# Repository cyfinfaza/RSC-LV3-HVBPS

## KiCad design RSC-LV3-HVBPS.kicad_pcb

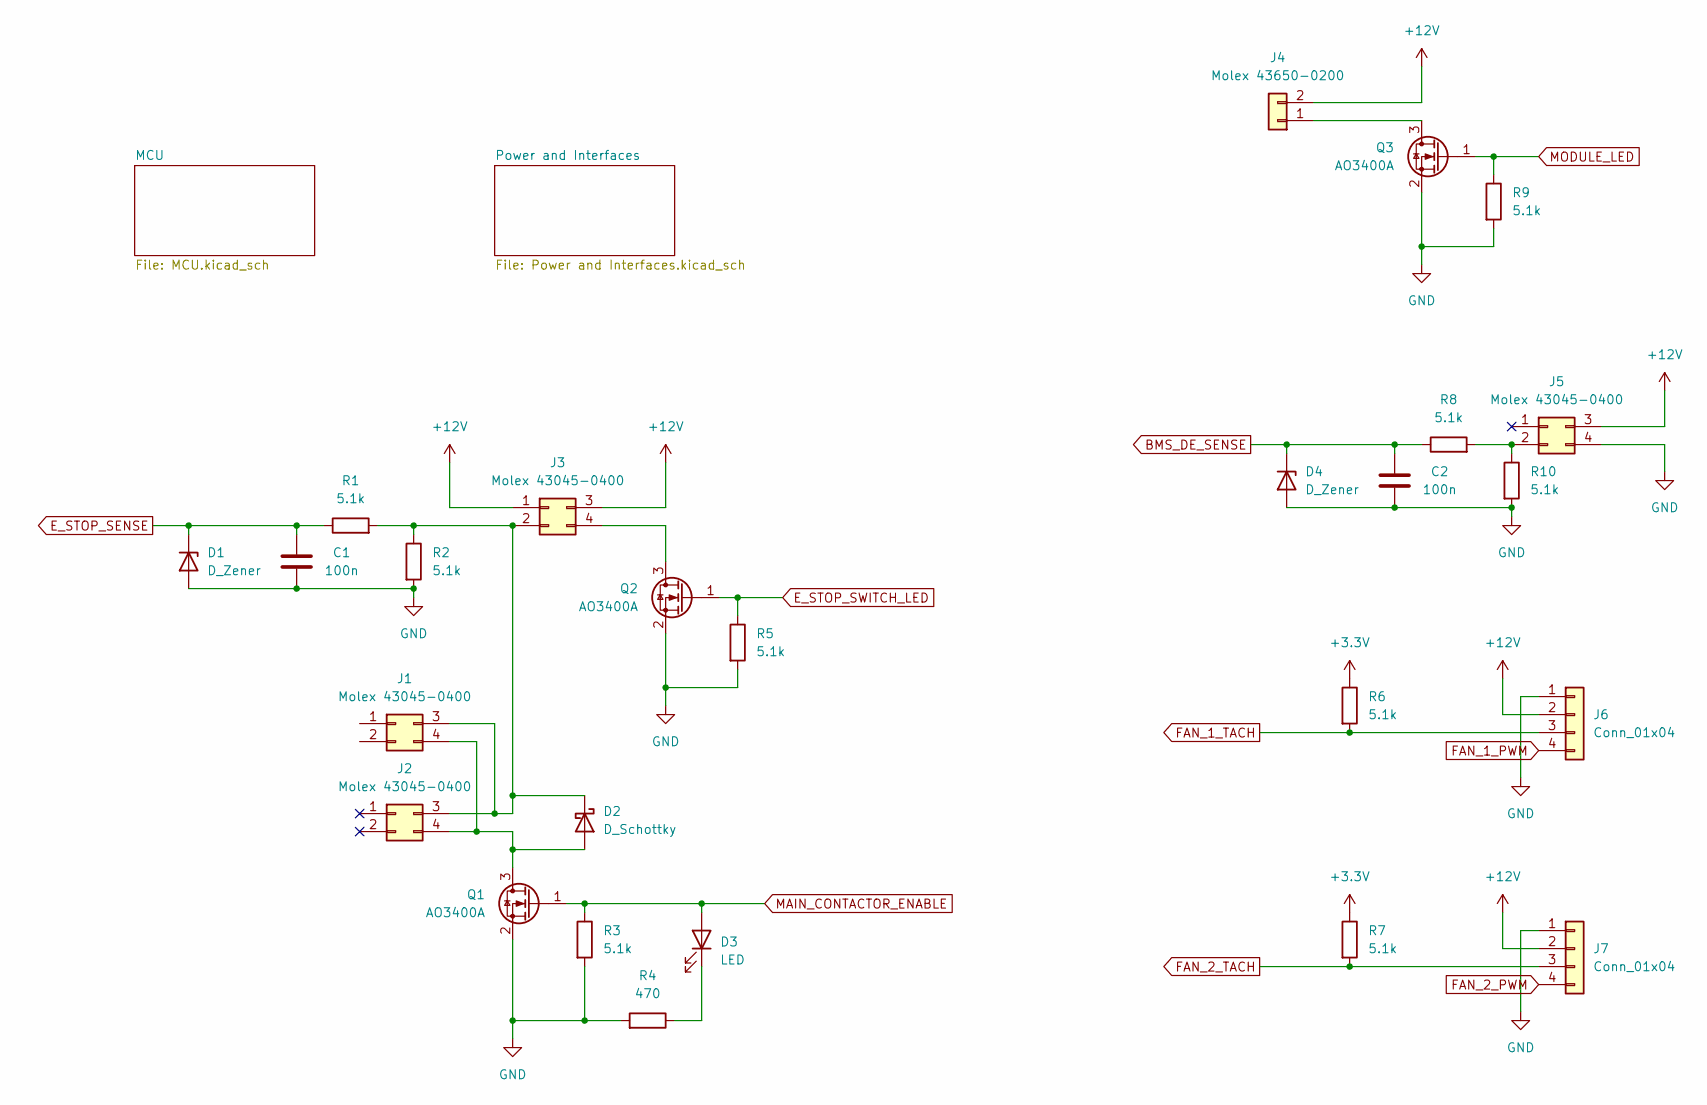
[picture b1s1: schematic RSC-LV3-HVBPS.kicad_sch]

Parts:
C1, C2: 100n; C_0603_1608Metric_Pad1.08x0.95mm_HandSolder
D1, D4: D_Zener; D_SOD-323_HandSoldering
D2: D_Schottky; D_SOD-123F
D3: LED; LED_0603_1608Metric_Pad1.05x0.95mm_HandSolder
J1, J2, J3, J5: Molex 43045-0400; Molex_Micro-Fit_3.0_43045-0412_2x02_P3.00mm_Vertical
J4: Molex 43650-0200; Molex_Micro-Fit_3.0_43650-0215_1x02_P3.00mm_Vertical
J6, J7: Conn_01x04; Molex_KK-254_AE-6410-04A_1x04_P2.54mm_Vertical
Q1, Q2, Q3: AO3400A; SOT-23
R1, R2, R3, R5, R6, R7, R8, R9, R10: 5.1k; R_0603_1608Metric_Pad0.98x0.95mm_HandSolder
R4: 470; R_0603_1608Metric_Pad0.98x0.95mm_HandSolder

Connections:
+3.3V: R6.1, R7.1; also elsewhere on the board
+12V: J3.1, J3.3, J4.2, J5.3, J6.2, J7.2; also elsewhere on the board
BMS_DE_SENSE: C2.1, D4.1 (K), R8.1; also elsewhere on the board
E_STOP_SENSE: C1.1, D1.1 (K), R1.1; also elsewhere on the board
E_STOP_SWITCH_LED: Q2.1 (G), R5.1; also elsewhere on the board
FAN_1_PWM: J6.4; also elsewhere on the board
FAN_1_TACH: J6.3, R6.2; also elsewhere on the board
FAN_2_PWM: J7.4; also elsewhere on the board
FAN_2_TACH: J7.3, R7.2; also elsewhere on the board
GND: C1.2, C2.2, D1.2 (A), D4.2 (A), J5.4, J6.1, J7.1, Q1.2 (S), Q2.2 (S), Q3.2 (S), R2.2, R3.2, R4.2, R5.2, R9.2, R10.2; also elsewhere on the board
MAIN_CONTACTOR_ENABLE: D3.2 (A), Q1.1 (G), R3.1; also elsewhere on the board
MODULE_LED: Q3.1 (G), R9.1; also elsewhere on the board
unnamed: D2.2 (A), J1.4, J2.4, Q1.3 (D)
unnamed: D2.1 (K), J1.3, J2.3, J3.2, R1.2, R2.1
unnamed: D3.1 (K), R4.1
unnamed: J3.4, Q2.3 (D)
unnamed: J4.1, Q3.3 (D)
unnamed: J5.2, R8.2, R10.1

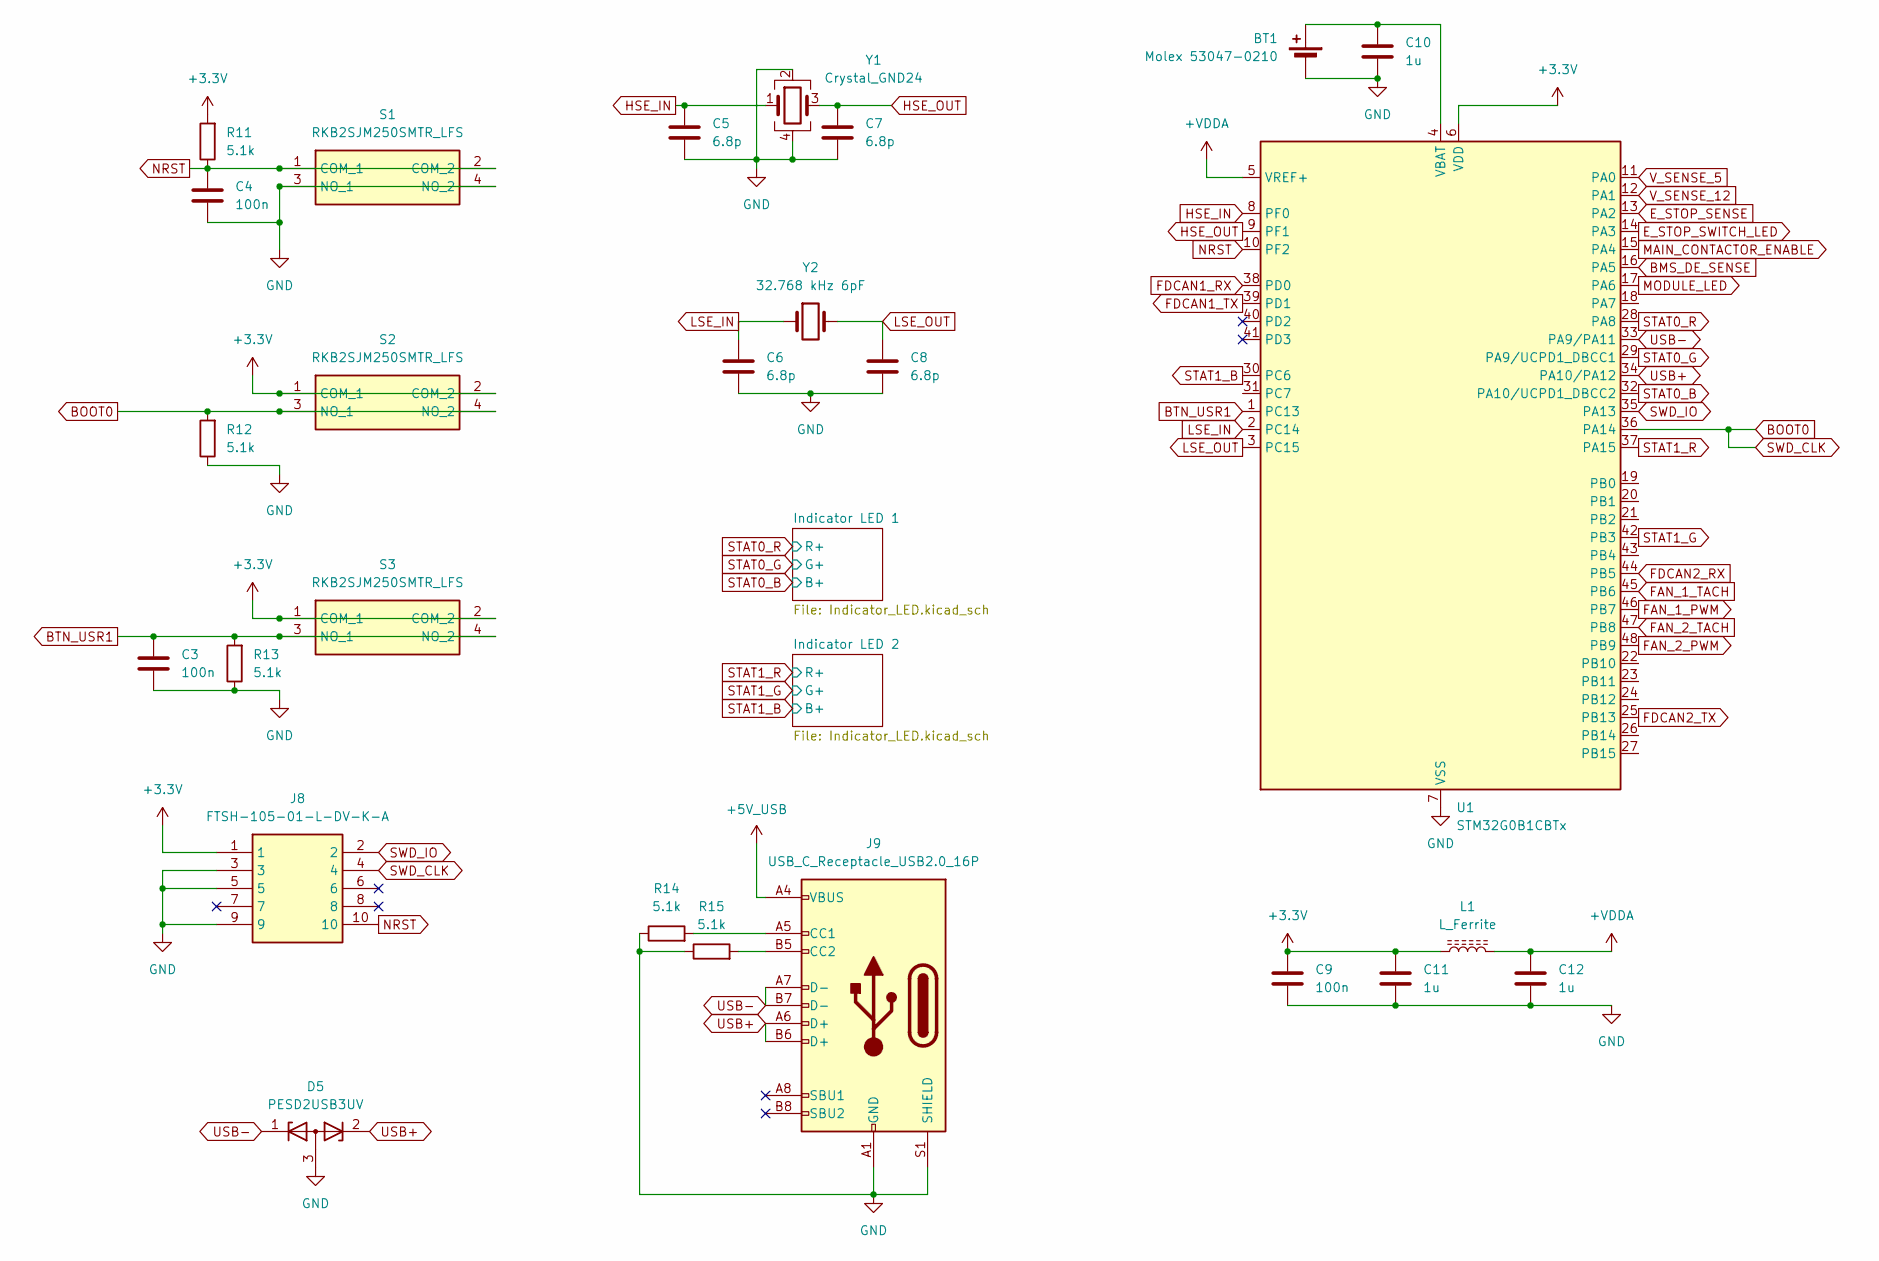
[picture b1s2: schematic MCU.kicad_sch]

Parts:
BT1: Molex 53047-0210; Molex_PicoBlade_53047-0210_1x02_P1.25mm_Vertical
C3, C4, C9: 100n; C_0603_1608Metric_Pad1.08x0.95mm_HandSolder
C5, C6, C7, C8: 6.8p; C_0603_1608Metric_Pad1.08x0.95mm_HandSolder
C10, C11, C12: 1u; C_0603_1608Metric_Pad1.08x0.95mm_HandSolder
D5: PESD2USB3UV; SOT-23W
J8: FTSH-105-01-L-DV-K-A; FTSH-105-XX-YYY-DV-K-A; Mouser Part Number 200-FTSH10501LDVKA
J9: USB_C_Receptacle_USB2.0_16P; USB_C_Receptacle_HRO_TYPE-C-31-M-12
L1: L_Ferrite; L_0603_1608Metric_Pad1.05x0.95mm_HandSolder
R11, R12, R13, R14, R15: 5.1k; R_0603_1608Metric_Pad0.98x0.95mm_HandSolder
S1, S2, S3: RKB2SJM250SMTR_LFS; RKB2SJM250SMTRLFS; Mouser Part Number 611-RKB2SJM250SMTRLF
U1: STM32G0B1CBTx; LQFP-48_7x7mm_P0.5mm
Y1: Crystal_GND24; Crystal_SMD_3225-4Pin_3.2x2.5mm
Y2: 32.768 kHz 6pF; Crystal_C26-LF_D2.1mm_L6.5mm_Horizontal

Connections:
+3.3V: C9.1, C11.1, J8.1, L1.1, R11.2, S2.1 (COM_1), S2.2 (COM_2), S3.1 (COM_1), S3.2 (COM_2), U1.6 (VDD); also elsewhere on the board
+5V_USB: J9.A4 (VBUS), J9.A9 (VBUS), J9.B4 (VBUS), J9.B9 (VBUS); also elsewhere on the board
+VDDA: C12.1, L1.2, U1.5 (VREF+)
BMS_DE_SENSE: U1.16 (PA5); also elsewhere on the board
BOOT0: J8.4, R12.2, S2.3 (NO_1), S2.4 (NO_2), U1.36 (PA14)
BTN_USR1: C3.1, R13.2, S3.3 (NO_1), S3.4 (NO_2), U1.1 (PC13)
E_STOP_SENSE: U1.13 (PA2); also elsewhere on the board
E_STOP_SWITCH_LED: U1.14 (PA3); also elsewhere on the board
FAN_1_PWM: U1.46 (PB7); also elsewhere on the board
FAN_1_TACH: U1.45 (PB6); also elsewhere on the board
FAN_2_PWM: U1.48 (PB9); also elsewhere on the board
FAN_2_TACH: U1.47 (PB8); also elsewhere on the board
FDCAN1_RX: U1.38 (PD0); also elsewhere on the board
FDCAN1_TX: U1.39 (PD1); also elsewhere on the board
FDCAN2_RX: U1.44 (PB5); also elsewhere on the board
FDCAN2_TX: U1.25 (PB13); also elsewhere on the board
GND: BT1.2 (-), C3.2, C4.2, C5.2, C6.2, C7.2, C8.2, C9.2, C10.2, C11.2, C12.2, D5.3 (A), J8.3, J8.5, J8.9, J9.A1 (GND), J9.A12 (GND), J9.B1 (GND), J9.B12 (GND), J9.S1 (SHIELD), R12.1, R13.1, R14.1, R15.1, S1.3 (NO_1), S1.4 (NO_2), U1.7 (VSS), Y1.2, Y1.4; also elsewhere on the board
HSE_IN: C5.1, U1.8 (PF0), Y1.1
HSE_OUT: C7.1, U1.9 (PF1), Y1.3
LSE_IN: C6.1, U1.2 (PC14), Y2.1
LSE_OUT: C8.1, U1.3 (PC15), Y2.2
MAIN_CONTACTOR_ENABLE: U1.15 (PA4); also elsewhere on the board
MODULE_LED: U1.17 (PA6); also elsewhere on the board
NRST: C4.1, J8.10, R11.1, S1.1 (COM_1), S1.2 (COM_2), U1.10 (PF2)
unnamed: BT1.1 (+), C10.1, U1.4 (VBAT)
unnamed: J9.A5 (CC1), R14.2
unnamed: J9.B5 (CC2), R15.2
STAT0_B: U1.32 (PA10/UCPD1_DBCC2); also elsewhere on the board
STAT0_G: U1.29 (PA9/UCPD1_DBCC1); also elsewhere on the board
STAT0_R: U1.28 (PA8); also elsewhere on the board
STAT1_B: U1.30 (PC6); also elsewhere on the board
STAT1_G: U1.42 (PB3); also elsewhere on the board
STAT1_R: U1.37 (PA15); also elsewhere on the board
SWD_IO: J8.2, U1.35 (PA13)
USB+: D5.2 (K), J9.A6 (D+), J9.B6 (D+), U1.34 (PA10/PA12)
USB-: D5.1 (K), J9.A7 (D-), J9.B7 (D-), U1.33 (PA9/PA11)
V_SENSE_5: U1.11 (PA0); also elsewhere on the board
V_SENSE_12: U1.12 (PA1); also elsewhere on the board

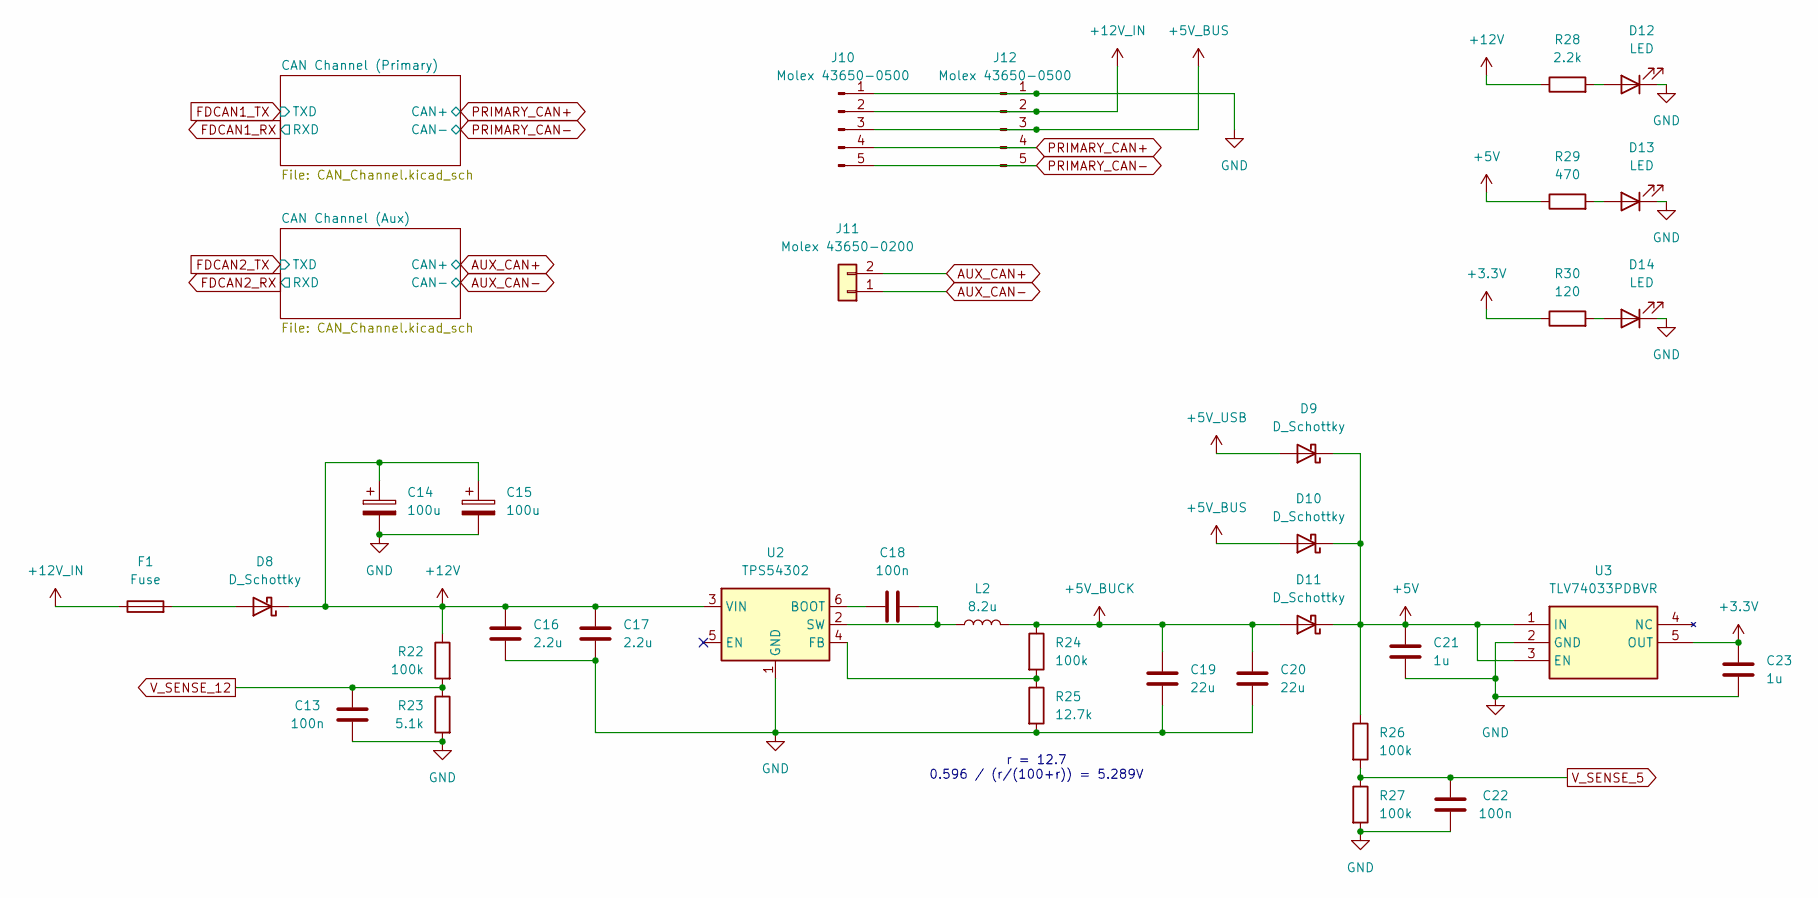
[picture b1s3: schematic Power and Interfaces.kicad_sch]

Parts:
C13, C18, C22: 100n; C_0603_1608Metric_Pad1.08x0.95mm_HandSolder
C14, C15: 100u; CP_Radial_D6.3mm_P2.50mm
C16, C17: 2.2u; C_0603_1608Metric_Pad1.08x0.95mm_HandSolder
C19, C20: 22u; C_1206_3216Metric_Pad1.33x1.80mm_HandSolder
C21, C23: 1u; C_0603_1608Metric_Pad1.08x0.95mm_HandSolder
D8: D_Schottky; D_SMA
D9, D10, D11: D_Schottky; D_SOD-123F
D12, D13, D14: LED; LED_0603_1608Metric_Pad1.05x0.95mm_HandSolder
F1: Fuse; Fuseholder_Blade_Mini_Keystone_3568
J10, J12: Molex 43650-0500; Molex_Micro-Fit_3.0_43650-0515_1x05_P3.00mm_Vertical
J11: Molex 43650-0200; Molex_Micro-Fit_3.0_43650-0215_1x02_P3.00mm_Vertical
L2: 8.2u; L_Abracon_ASPI-4030S
R22, R24, R26, R27: 100k; R_0603_1608Metric_Pad0.98x0.95mm_HandSolder
R23: 5.1k; R_0603_1608Metric_Pad0.98x0.95mm_HandSolder
R25: 12.7k; R_0603_1608Metric_Pad0.98x0.95mm_HandSolder
R28: 2.2k; R_0603_1608Metric_Pad0.98x0.95mm_HandSolder
R29: 470; R_0603_1608Metric_Pad0.98x0.95mm_HandSolder
R30: 120; R_0603_1608Metric_Pad0.98x0.95mm_HandSolder
U2: TPS54302; SOT-23-6_Handsoldering
U3: TLV74033PDBVR; SOT95P280X145-5N; Mouser Part Number 595-TLV74033PDBVR

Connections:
+3.3V: C23.1, R30.1, U3.5 (OUT); also elsewhere on the board
+5V: C21.1, D9.1 (K), D10.1 (K), D11.1 (K), R26.1, R29.1, U3.1 (IN), U3.3 (EN); also elsewhere on the board
+5V_BUCK: C19.1, C20.1, D11.2 (A), L2.2, R24.1
+5V_BUS: D10.2 (A), J10.3, J12.3
+5V_USB: D9.2 (A); also elsewhere on the board
+12V: C14.1, C15.1, C16.1, C17.1, D8.1 (K), R22.1, R28.1, U2.3 (VIN); also elsewhere on the board
+12V_IN: F1.1, J10.2, J12.2
AUX_CAN+: J11.2; also elsewhere on the board
AUX_CAN-: J11.1; also elsewhere on the board
GND: C13.2, C14.2, C15.2, C16.2, C17.2, C19.2, C20.2, C21.2, C22.2, C23.2, D12.1 (K), D13.1 (K), D14.1 (K), J10.1, J12.1, R23.2, R25.2, R27.2, U2.1 (GND), U3.2 (GND); also elsewhere on the board
unnamed: D8.2 (A), F1.2
unnamed: D12.2 (A), R28.2
unnamed: D13.2 (A), R29.2
unnamed: D14.2 (A), R30.2
unnamed: C18.1, U2.6 (BOOT)
unnamed: R24.2, R25.1, U2.4 (FB)
unnamed: C18.2, L2.1, U2.2 (SW)
PRIMARY_CAN+: J10.4, J12.4; also elsewhere on the board
PRIMARY_CAN-: J10.5, J12.5; also elsewhere on the board
V_SENSE_5: C22.1, R26.2, R27.1; also elsewhere on the board
V_SENSE_12: C13.1, R22.2, R23.1; also elsewhere on the board

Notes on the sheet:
r = 12.7 0.596 / (r/(100+r)) = 5.289V

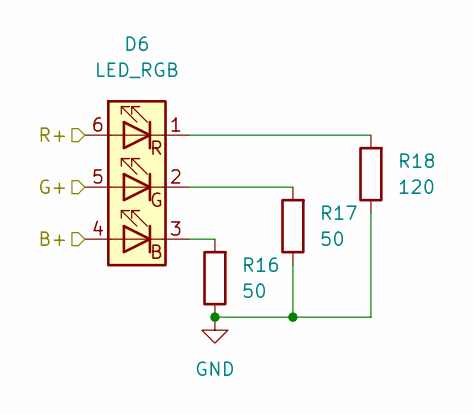
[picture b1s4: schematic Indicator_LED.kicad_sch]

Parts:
D6: LED_RGB; LED_RGB_5050-6
R16, R17: 50; R_0603_1608Metric_Pad0.98x0.95mm_HandSolder
R18: 120; R_0603_1608Metric_Pad0.98x0.95mm_HandSolder

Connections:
GND: R16.1, R17.1, R18.1; also elsewhere on the board
unnamed: D6.3 (BK), R16.2
unnamed: D6.2 (GK), R17.2
unnamed: D6.1 (RK), R18.2
STAT0_B: D6.4 (BA); also elsewhere on the board
STAT0_G: D6.5 (GA); also elsewhere on the board
STAT0_R: D6.6 (RA); also elsewhere on the board

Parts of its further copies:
D7: LED_RGB; LED_RGB_5050-6
R19, R20: 50; R_0603_1608Metric_Pad0.98x0.95mm_HandSolder
R21: 120; R_0603_1608Metric_Pad0.98x0.95mm_HandSolder

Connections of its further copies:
GND: R19.1, R20.1, R21.1; also elsewhere on the board
unnamed: D7.3 (BK), R19.2
unnamed: D7.2 (GK), R20.2
unnamed: D7.1 (RK), R21.2
STAT1_B: D7.4 (BA); also elsewhere on the board
STAT1_G: D7.5 (GA); also elsewhere on the board
STAT1_R: D7.6 (RA); also elsewhere on the board

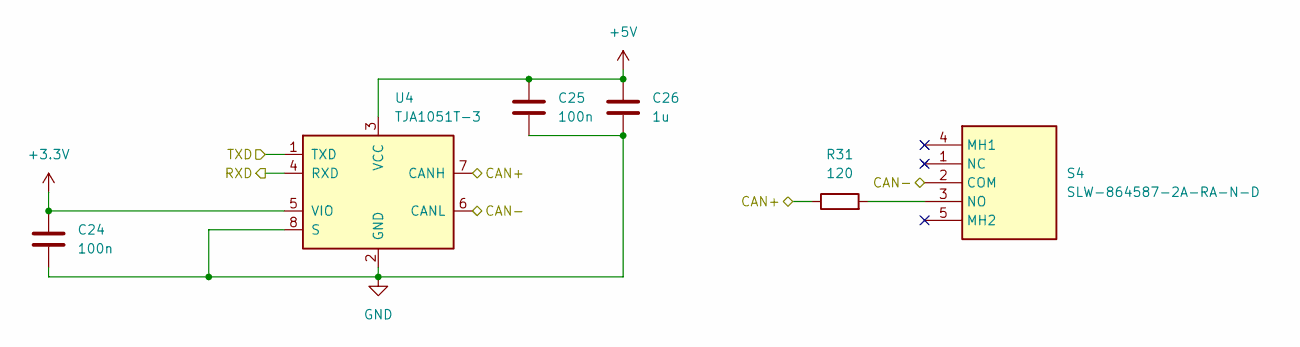
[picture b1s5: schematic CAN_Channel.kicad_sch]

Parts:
C24, C25: 100n; C_0603_1608Metric_Pad1.08x0.95mm_HandSolder
C26: 1u; C_0603_1608Metric_Pad1.08x0.95mm_HandSolder
R31: 120; R_0603_1608Metric_Pad0.98x0.95mm_HandSolder
S4: SLW-864587-2A-RA-N-D; SLW8645872ARAND; Mouser Part Number 179-SLW8645872ARAND
U4: TJA1051T-3; SOIC-8_3.9x4.9mm_P1.27mm

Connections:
+3.3V: C24.1, U4.5 (VIO); also elsewhere on the board
+5V: C25.1, C26.1, U4.3 (VCC); also elsewhere on the board
FDCAN1_RX: U4.4 (RXD); also elsewhere on the board
FDCAN1_TX: U4.1 (TXD); also elsewhere on the board
GND: C24.2, C25.2, C26.2, U4.2 (GND), U4.8 (S); also elsewhere on the board
unnamed: R31.2, S4.3 (NO)
PRIMARY_CAN+: R31.1, U4.7 (CANH); also elsewhere on the board
PRIMARY_CAN-: S4.2 (COM), U4.6 (CANL); also elsewhere on the board

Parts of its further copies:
C27, C28: 100n; C_0603_1608Metric_Pad1.08x0.95mm_HandSolder
C29: 1u; C_0603_1608Metric_Pad1.08x0.95mm_HandSolder
R32: 120; R_0603_1608Metric_Pad0.98x0.95mm_HandSolder
S5: SLW-864587-2A-RA-N-D; SLW8645872ARAND; Mouser Part Number 179-SLW8645872ARAND
U5: TJA1051T-3; SOIC-8_3.9x4.9mm_P1.27mm

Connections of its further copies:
+3.3V: C27.1, U5.5 (VIO); also elsewhere on the board
+5V: C28.1, C29.1, U5.3 (VCC); also elsewhere on the board
AUX_CAN+: R32.1, U5.7 (CANH); also elsewhere on the board
AUX_CAN-: S5.2 (COM), U5.6 (CANL); also elsewhere on the board
FDCAN2_RX: U5.4 (RXD); also elsewhere on the board
FDCAN2_TX: U5.1 (TXD); also elsewhere on the board
GND: C27.2, C28.2, C29.2, U5.2 (GND), U5.8 (S); also elsewhere on the board
unnamed: R32.2, S5.3 (NO)

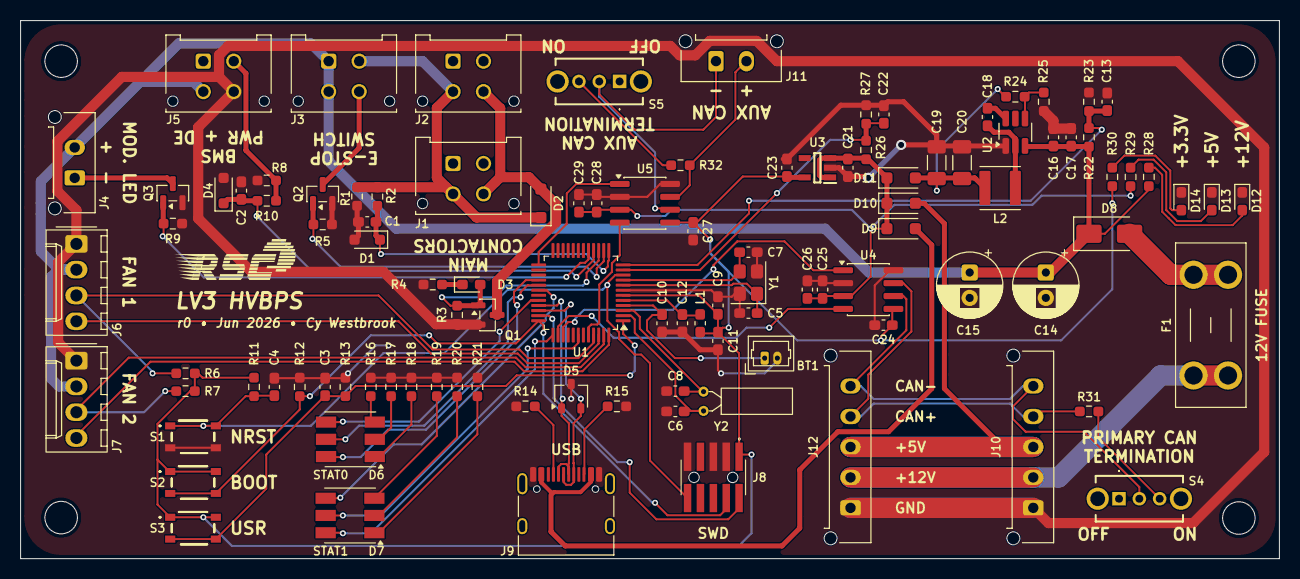
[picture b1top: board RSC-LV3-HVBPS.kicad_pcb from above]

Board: 2 copper layers, 124.0 x 53.0 mm, 106 parts (0 on the bottom side), 68 nets.

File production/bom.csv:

Designator,Footprint,Quantity,Value,LCSC Part #
BT1,Molex_PicoBlade_53047-0210_1x02_P1.25mm_Vertical,1,Molex 53047-0210,
"C1, C13, C18, C2, C22, C24, C25, C27, C28, C3, C4, C9",0603,12,100n,
"C10, C11, C12, C21, C23, C26, C29",0603,7,1u,
"C14, C15",CP_Radial_D6.3mm_P2.50mm,2,100u,
"C16, C17",0603,2,2.2u,
"C19, C20",1206,2,22u,
"C5, C6, C7, C8",0603,4,6.8p,
"D1, D4",D_SOD-323_HandSoldering,2,D_Zener,
"D10, D11, D2, D9",D_SOD-123F,4,D_Schottky,
"D12, D13, D14, D3",0603,4,LED,
D5,SOT-23W,1,PESD2USB3UV,
"D6, D7",LED_RGB_5050-6,2,LED_RGB,
D8,D_SMA,1,D_Schottky,
F1,Fuseholder_Blade_Mini_Keystone_3568,1,Fuse,
"J1, J2, J3, J5",Molex_Micro-Fit_3.0_43045-0412_2x02_P3.00mm_Vertical,4,Molex 43045-0400,
"J10, J12",Molex_Micro-Fit_3.0_43650-0515_1x05_P3.00mm_Vertical,2,Molex 43650-0500,
"J11, J4",Molex_Micro-Fit_3.0_43650-0215_1x02_P3.00mm_Vertical,2,Molex 43650-0200,
"J6, J7",Molex_KK-254_AE-6410-04A_1x04_P2.54mm_Vertical,2,Conn_01x04,
J8,FTSH-105-XX-YYY-DV-K-A,1,FTSH-105-01-L-DV-K-A,
J9,USB_C_Receptacle_HRO_TYPE-C-31-M-12,1,USB_C_Receptacle_USB2.0_16P,
L1,0603,1,L_Ferrite,
L2,L_Abracon_ASPI-4030S,1,8.2u,
"Q1, Q2, Q3",SOT-23,3,AO3400A,
"R1, R10, R11, R12, R13, R14, R15, R2, R23, R3, R5, R6, R7, R8, R9",0603,15,5.1k,
"R16, R17, R19, R20",0603,4,50,
"R18, R21, R30, R31, R32",0603,5,120,
"R22, R24, R26, R27",0603,4,100k,
R25,0603,1,12.7k,
R28,0603,1,2.2k,
"R29, R4",0603,2,470,
"S1, S2, S3",RKB2SJM250SMTRLFS,3,RKB2SJM250SMTR_LFS,
"S4, S5",SLW8645872ARAND,2,SLW-864587-2A-RA-N-D,
U1,LQFP-48_7x7mm_P0.5mm,1,STM32G0B1CBTx,
U2,SOT-23-6_Handsoldering,1,TPS54302,
U3,SOT95P280X145-5N,1,TLV74033PDBVR,
"U4, U5",SOIC-8_3.9x4.9mm_P1.27mm,2,TJA1051T-3,
Y1,Crystal_SMD_3225-4Pin_3.2x2.5mm,1,Crystal_GND24,
Y2,Crystal_C26-LF_D2.1mm_L6.5mm_Horizontal,1,32.768 kHz 6pF,

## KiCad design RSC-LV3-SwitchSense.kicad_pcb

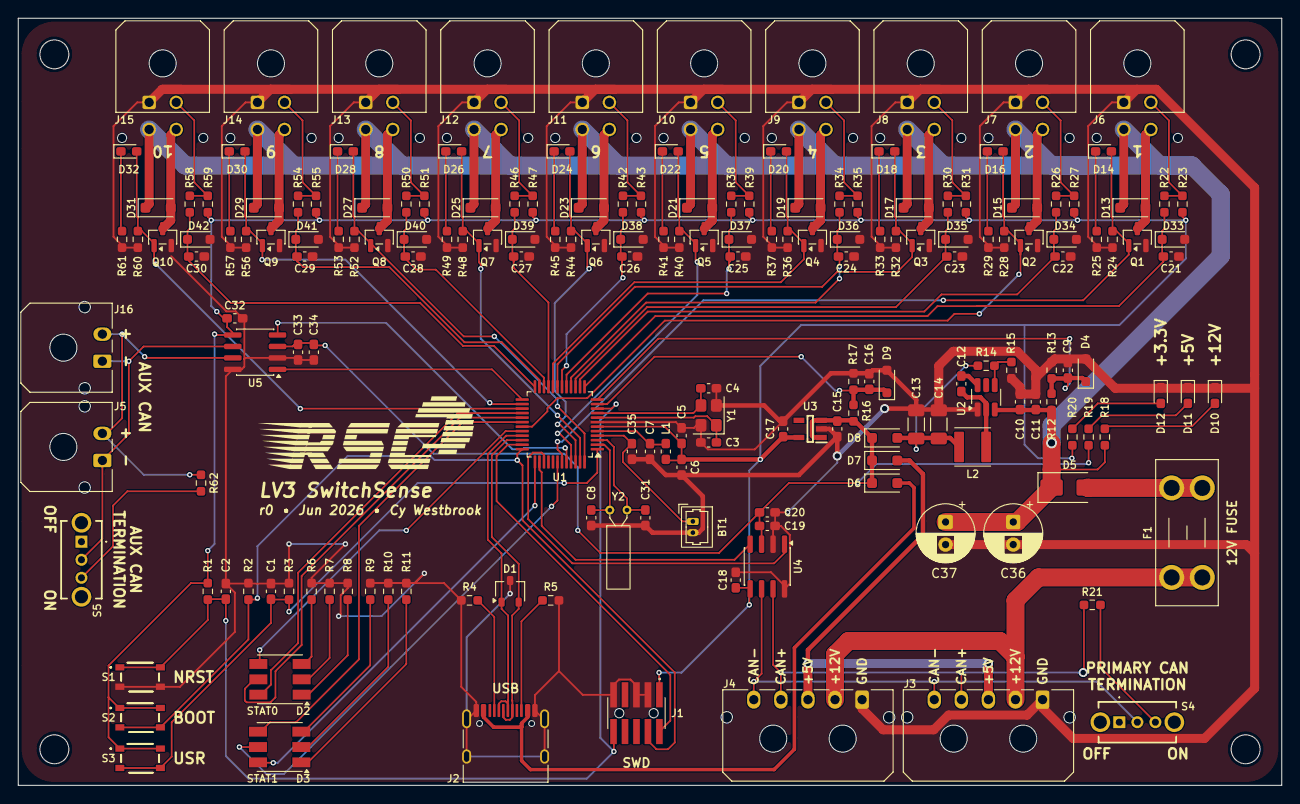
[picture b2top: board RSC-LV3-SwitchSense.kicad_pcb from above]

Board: 2 copper layers, 140.0 x 85.0 mm, 183 parts (0 on the bottom side), 103 nets.

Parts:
BT1: Molex 53047-0210; Molex_PicoBlade_53047-0210_1x02_P1.25mm_Vertical
C1, C2, C5, C9, C12, C16, C18, C19, C21, C22, C23, C24, C25, C26, C27, C28, C29, C30, C32, C33: 100n; C_0603_1608Metric_Pad1.08x0.95mm_HandSolder
C3, C4, C8, C31: 6.8p; C_0603_1608Metric_Pad1.08x0.95mm_HandSolder
C6, C7, C15, C17, C20, C34, C35: 1u; C_0603_1608Metric_Pad1.08x0.95mm_HandSolder
C10, C11: 2.2u; C_0603_1608Metric_Pad1.08x0.95mm_HandSolder
C13, C14: 22u; C_1206_3216Metric_Pad1.33x1.80mm_HandSolder
C36, C37: 100u; CP_Radial_D6.3mm_P2.50mm
D1: PESD2USB3UV; SOT-23W
D2, D3: LED_RGB; LED_RGB_5050-6
D4, D9, D33, D34, D35, D36, D37, D38, D39, D40, D41, D42: D_Zener; D_SOD-323_HandSoldering
D5: D_Schottky; D_SMA
D6, D7, D8, D13, D15, D17, D19, D21, D23, D25, D27, D29, D31: D_Schottky; D_SOD-123F
D10, D11, D12, D14, D16, D18, D20, D22, D24, D26, D28, D30, D32: LED; LED_0603_1608Metric_Pad1.05x0.95mm_HandSolder
F1: Fuse; Fuseholder_Blade_Mini_Keystone_3568
J1: FTSH-105-01-L-DV-K-A; FTSH-105-XX-YYY-DV-K-A
J2: USB_C_Receptacle_USB2.0_16P; USB_C_Receptacle_HRO_TYPE-C-31-M-12
J3, J4: Molex 43650-0500; Molex_Micro-Fit_3.0_43650-0500_1x05_P3.00mm_Horizontal_Vert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
J5, J16: Molex 43650-0200; Molex_Micro-Fit_3.0_43650-0200_1x02_P3.00mm_Horizontal_Vert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
J6, J7, J8, J9, J10, J11, J12, J13, J14, J15: Molex 43045-0400; Molex_Micro-Fit_3.0_43045-0400_2x02_P3.00mm_Horizontal_Vert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
L1: L_Ferrite; L_0603_1608Metric_Pad1.05x0.95mm_HandSolder
L2: 8.2u; L_Abracon_ASPI-4030S
Q1, Q2, Q3, Q4, Q5, Q6, Q7, Q8, Q9, Q10: AO3400A; SOT-23
R1, R2, R3, R4, R5, R13, R22, R23, R24, R26, R27, R28, R30, R31, R32, R34, R35, R36, R38, R39, R40, R42, R43, R44, R46, R47, R48, R50, R51, R52, R54, R55, R56, R58, R59, R60: 5.1k; R_0603_1608Metric_Pad0.98x0.95mm_HandSolder
R6, R7, R9, R10: 50; R_0603_1608Metric_Pad0.98x0.95mm_HandSolder
R8, R11, R20, R21, R62: 120; R_0603_1608Metric_Pad0.98x0.95mm_HandSolder
R12, R14, R16, R17: 100k; R_0603_1608Metric_Pad0.98x0.95mm_HandSolder
R15: 12.7k; R_0603_1608Metric_Pad0.98x0.95mm_HandSolder
R18: 2.2k; R_0603_1608Metric_Pad0.98x0.95mm_HandSolder
R19, R25, R29, R33, R37, R41, R45, R49, R53, R57, R61: 470; R_0603_1608Metric_Pad0.98x0.95mm_HandSolder
S1, S2, S3: RKB2SJM250SMTR_LFS; RKB2SJM250SMTRLFS
S4, S5: SLW-864587-2A-RA-N-D; SLW8645872ARAND
U1: STM32G0B1CBTx; LQFP-48_7x7mm_P0.5mm
U2: TPS54302; SOT-23-6_Handsoldering
U3: TLV74033PDBVR; SOT95P280X145-5N
U4, U5: TJA1051T-3; SOIC-8_3.9x4.9mm_P1.27mm
Y1: Crystal_GND24; Crystal_SMD_3225-4Pin_3.2x2.5mm
Y2: 32.768 kHz 6pF; Crystal_C26-LF_D2.1mm_L6.5mm_Horizontal

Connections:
+3.3V: C5.1, C6.1, C17.1, C18.1, C32.1, J1.1, L1.1, R1.2, R20.1, R23.1, R27.1, R31.1, R35.1, R39.1, R43.1, R47.1, R51.1, R55.1, R59.1, S2.1 (COM_1), S2.2 (COM_2), S3.1 (COM_1), S3.2 (COM_2), U1.6 (VDD), U3.5 (OUT), U4.5 (VIO), U5.5 (VIO)
+5V: C15.1, C19.1, C20.1, C33.1, C34.1, D6.1 (K), D7.1 (K), D8.1 (K), R16.1, R19.1, U3.1 (IN), U3.3 (EN), U4.3 (VCC), U5.3 (VCC)
+5V_BUCK: C13.1, C14.1, D8.2 (A), L2.2, R14.1
+5V_BUS: D7.2 (A), J3.3, J4.3
+5V_USB: D6.2 (A), J2.A4 (VBUS), J2.A9 (VBUS), J2.B4 (VBUS), J2.B9 (VBUS)
+12V: C10.1, C11.1, C36.1, C37.1, D5.1 (K), D13.1 (K), D15.1 (K), D17.1 (K), D19.1 (K), D21.1 (K), D23.1 (K), D25.1 (K), D27.1 (K), D29.1 (K), D31.1 (K), J6.3, J7.3, J8.3, J9.3, J10.3, J11.3, J12.3, J13.3, J14.3, J15.3, R12.1, R18.1, U2.3 (VIN)
+12V_IN: F1.1, J3.2, J4.2
+VDDA: C7.1, L1.2, U1.5 (VREF+)
AUX_CAN+: J5.2, J16.2, R62.1, U5.7 (CANH)
AUX_CAN-: J5.1, J16.1, S5.2 (COM), U5.6 (CANL)
BOOT0: J1.4, R2.2, S2.3 (NO_1), S2.4 (NO_2), U1.36 (PA14)
BTN_USR1: C1.1, R3.2, S3.3 (NO_1), S3.4 (NO_2), U1.1 (PC13)
FDCAN1_RX: U1.38 (PD0), U4.4 (RXD)
FDCAN1_TX: U1.39 (PD1), U4.1 (TXD)
FDCAN2_RX: U1.44 (PB5), U5.4 (RXD)
FDCAN2_TX: U1.25 (PB13), U5.1 (TXD)
GND: BT1.2 (-), C1.2, C2.2, C3.2, C4.2, C5.2, C6.2, C7.2, C8.2, C9.2, C10.2, C11.2, C13.2, C14.2, C15.2, C16.2, C17.2, C18.2, C19.2, C20.2, C21.2, C22.2, C23.2, C24.2, C25.2, C26.2, C27.2, C28.2, C29.2, C30.2, C31.2, C32.2, C33.2, C34.2, C35.2, C36.2, C37.2, D1.3 (A), D4.2 (A), D9.2 (A), D10.1 (K), D11.1 (K), D12.1 (K), D33.2 (A), D34.2 (A), D35.2 (A), D36.2 (A), D37.2 (A), D38.2 (A), D39.2 (A), D40.2 (A), D41.2 (A), D42.2 (A), J1.3, J1.5, J1.9, J2.A1 (GND), J2.A12 (GND), J2.B1 (GND), J2.B12 (GND), J2.SH, J3.1, J4.1, J6.1, J7.1, J8.1, J9.1, J10.1, J11.1, J12.1, J13.1, J14.1, J15.1, Q1.2 (S), Q2.2 (S), Q3.2 (S), Q4.2 (S), Q5.2 (S), Q6.2 (S), Q7.2 (S), Q8.2 (S), Q9.2 (S), Q10.2 (S), R2.1, R3.1, R4.1, R5.1, R6.1, R7.1, R8.1, R9.1, R10.1, R11.1, R13.2, R15.2, R17.2, R24.2, R25.2, R28.2, R29.2, R32.2, R33.2, R36.2, R37.2, R40.2, R41.2, R44.2, R45.2, R48.2, R49.2, R52.2, R53.2, R56.2, R57.2, R60.2, R61.2, S1.3 (NO_1), S1.4 (NO_2), U1.7 (VSS), U2.1 (GND), U3.2 (GND), U4.2 (GND), U4.8 (S), U5.2 (GND), U5.8 (S), Y1.2, Y1.4
HSE_IN: C3.1, U1.8 (PF0), Y1.1
HSE_OUT: C4.1, U1.9 (PF1), Y1.3
IN_1: C21.1, D33.1 (K), R22.1, U1.13 (PA2)
IN_2: C22.1, D34.1 (K), R26.1, U1.14 (PA3)
IN_3: C23.1, D35.1 (K), R30.1, U1.15 (PA4)
IN_4: C24.1, D36.1 (K), R34.1, U1.16 (PA5)
IN_5: C25.1, D37.1 (K), R38.1, U1.17 (PA6)
IN_6: C26.1, D38.1 (K), R42.1, U1.18 (PA7)
IN_7: C27.1, D39.1 (K), R46.1, U1.21 (PB2)
IN_8: C28.1, D40.1 (K), R50.1, U1.22 (PB10)
IN_9: C29.1, D41.1 (K), R54.1, U1.23 (PB11)
IN_10: C30.1, D42.1 (K), R58.1, U1.24 (PB12)
LSE_IN: C8.1, U1.2 (PC14), Y2.1
LSE_OUT: C31.1, U1.3 (PC15), Y2.2
NRST: C2.1, J1.10, R1.1, S1.1 (COM_1), S1.2 (COM_2), U1.10 (PF2)
unnamed: BT1.1 (+), C35.1, U1.4 (VBAT)
unnamed: D2.3 (BK), R6.2
unnamed: D2.2 (GK), R7.2
unnamed: D2.1 (RK), R8.2
unnamed: D3.3 (BK), R9.2
unnamed: D3.2 (GK), R10.2
unnamed: D3.1 (RK), R11.2
unnamed: D5.2 (A), F1.2
unnamed: D10.2 (A), R18.2
unnamed: D11.2 (A), R19.2
unnamed: D12.2 (A), R20.2
unnamed: D13.2 (A), J6.4, Q1.3 (D)
unnamed: D14.1 (K), R25.1
unnamed: D15.2 (A), J7.4, Q2.3 (D)
unnamed: D16.1 (K), R29.1
unnamed: D17.2 (A), J8.4, Q3.3 (D)
unnamed: D18.1 (K), R33.1
unnamed: D19.2 (A), J9.4, Q4.3 (D)
unnamed: D20.1 (K), R37.1
unnamed: D21.2 (A), J10.4, Q5.3 (D)
unnamed: D22.1 (K), R41.1
unnamed: D23.2 (A), J11.4, Q6.3 (D)
unnamed: D24.1 (K), R45.1
unnamed: D25.2 (A), J12.4, Q7.3 (D)
unnamed: D26.1 (K), R49.1
unnamed: D27.2 (A), J13.4, Q8.3 (D)
unnamed: D28.1 (K), R53.1
unnamed: D29.2 (A), J14.4, Q9.3 (D)
unnamed: D30.1 (K), R57.1
unnamed: D31.2 (A), J15.4, Q10.3 (D)
unnamed: D32.1 (K), R61.1
unnamed: J2.A5 (CC1), R4.2
unnamed: J2.B5 (CC2), R5.2
unnamed: J6.2, R22.2, R23.2
unnamed: J7.2, R26.2, R27.2
unnamed: J8.2, R30.2, R31.2
unnamed: J9.2, R34.2, R35.2
unnamed: J10.2, R38.2, R39.2
unnamed: J11.2, R42.2, R43.2
unnamed: J12.2, R46.2, R47.2
unnamed: J13.2, R50.2, R51.2
unnamed: J14.2, R54.2, R55.2
unnamed: J15.2, R58.2, R59.2
unnamed: R21.2, S4.3 (NO)
unnamed: R62.2, S5.3 (NO)
unnamed: C12.1, U2.6 (BOOT)
unnamed: R14.2, R15.1, U2.4 (FB)
unnamed: C12.2, L2.1, U2.2 (SW)
OUT_1: D14.2 (A), Q1.1 (G), R24.1, U1.43 (PB4)
OUT_2: D16.2 (A), Q2.1 (G), R28.1, U1.31 (PC7)
OUT_3: D18.2 (A), Q3.1 (G), R32.1, U1.19 (PB0)
OUT_4: D20.2 (A), Q4.1 (G), R36.1, U1.20 (PB1)
OUT_5: D22.2 (A), Q5.1 (G), R40.1, U1.45 (PB6)
OUT_6: D24.2 (A), Q6.1 (G), R44.1, U1.46 (PB7)
OUT_7: D26.2 (A), Q7.1 (G), R48.1, U1.47 (PB8)
OUT_8: D28.2 (A), Q8.1 (G), R52.1, U1.48 (PB9)
OUT_9: D30.2 (A), Q9.1 (G), R56.1, U1.26 (PB14)
OUT_10: D32.2 (A), Q10.1 (G), R60.1, U1.27 (PB15)
PRIMARY_CAN+: J3.4, J4.4, R21.1, U4.7 (CANH)
PRIMARY_CAN-: J3.5, J4.5, S4.2 (COM), U4.6 (CANL)
STAT0_B: D2.4 (BA), U1.32 (PA10/UCPD1_DBCC2)
STAT0_G: D2.5 (GA), U1.29 (PA9/UCPD1_DBCC1)
STAT0_R: D2.6 (RA), U1.28 (PA8)
STAT1_B: D3.4 (BA), U1.30 (PC6)
STAT1_G: D3.5 (GA), U1.42 (PB3)
STAT1_R: D3.6 (RA), U1.37 (PA15)
SWD_IO: J1.2, U1.35 (PA13)
USB+: D1.2 (K), J2.A6 (D+), J2.B6 (D+), U1.34 (PA10/PA12)
USB-: D1.1 (K), J2.A7 (D-), J2.B7 (D-), U1.33 (PA9/PA11)
V_SENSE_5: C16.1, D9.1 (K), R16.2, R17.1, U1.11 (PA0)
V_SENSE_12: C9.1, D4.1 (K), R12.2, R13.1, U1.12 (PA1)

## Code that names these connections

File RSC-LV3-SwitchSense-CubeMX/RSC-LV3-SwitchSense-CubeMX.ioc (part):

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Mcu.Name=STM32G0B1C(B-C-E)Tx
Mcu.Package=LQFP48
Mcu.UserName=STM32G0B1CBTx
PA0.GPIOParameters=GPIO_Label
PA0.GPIO_Label=V_SENSE_5
PA0.Mode=IN0
PA0.Signal=ADC1_IN0
PA1.GPIOParameters=GPIO_Label
PA1.GPIO_Label=V_SENSE_12
PA1.Mode=IN1
PA1.Signal=ADC1_IN1
PA10.GPIOParameters=GPIO_Label
PA10.GPIO_Label=STAT0_B
PA10.Signal=S_TIM1_CH3
PA11\ [PA9].Mode=Device
PA11\ [PA9].Signal=USB_DM
PA12\ [PA10].Mode=Device
PA12\ [PA10].Signal=USB_DP
PA13.Mode=Serial_Wire
PA13.Signal=SYS_SWDIO
PA14-BOOT0.Mode=Serial_Wire
PA14-BOOT0.Signal=SYS_SWCLK
PA15.GPIOParameters=GPIO_Label
PA15.GPIO_Label=STAT1_R
PA15.Signal=S_TIM2_CH1_ETR
PA2.GPIOParameters=GPIO_Label
PA2.GPIO_Label=IN_1
PA2.Mode=IN2
PA2.Signal=ADC1_IN2
PA3.GPIOParameters=GPIO_Label
PA3.GPIO_Label=IN_2
PA3.Mode=IN3
PA3.Signal=ADC1_IN3
PA4.GPIOParameters=GPIO_Label
PA4.GPIO_Label=IN_3
PA4.Mode=IN4
PA4.Signal=ADC1_IN4
PA5.GPIOParameters=GPIO_Label
PA5.GPIO_Label=IN_4
PA5.Mode=IN5
PA5.Signal=ADC1_IN5
PA6.GPIOParameters=GPIO_Label
PA6.GPIO_Label=IN_5
PA6.Mode=IN6
PA6.Signal=ADC1_IN6
PA7.GPIOParameters=GPIO_Label
PA7.GPIO_Label=IN_6
PA7.Mode=IN7
PA7.Signal=ADC1_IN7
PA8.GPIOParameters=GPIO_Label
PA8.GPIO_Label=STAT0_R
PA8.Signal=S_TIM1_CH1
PA9.GPIOParameters=GPIO_Label
PA9.GPIO_Label=STAT0_G
PA9.Signal=S_TIM1_CH2
PB0.GPIOParameters=GPIO_Label
PB0.GPIO_Label=OUT_3
PB0.Signal=S_TIM3_CH3
PB1.GPIOParameters=GPIO_Label
PB1.GPIO_Label=OUT_4
PB1.Signal=S_TIM3_CH4
PB10.GPIOParameters=GPIO_Label
PB10.GPIO_Label=IN_8
PB10.Mode=IN11
PB10.Signal=ADC1_IN11
PB11.GPIOParameters=GPIO_Label
PB11.GPIO_Label=IN_9
PB11.Mode=IN15
PB11.Signal=ADC1_IN15
PB12.GPIOParameters=GPIO_Label
PB12.GPIO_Label=IN_10
PB12.Mode=IN16
PB12.Signal=ADC1_IN16
PB13.Mode=FDCAN_Activate
PB13.Signal=FDCAN2_TX
PB14.GPIOParameters=GPIO_Label
PB14.GPIO_Label=OUT_9
PB14.Signal=S_TIM15_CH1
PB15.GPIOParameters=GPIO_Label
PB15.GPIO_Label=OUT_10
PB15.Signal=S_TIM15_CH2
PB2.GPIOParameters=GPIO_Label
PB2.GPIO_Label=IN_7
PB2.Mode=IN10
PB2.Signal=ADC1_IN10
PB3.GPIOParameters=GPIO_Label
PB3.GPIO_Label=STAT1_G
PB3.Signal=S_TIM2_CH2
PB4.GPIOParameters=GPIO_Label
PB4.GPIO_Label=OUT_1
PB4.Signal=S_TIM3_CH1
PB5.Mode=FDCAN_Activate
PB5.Signal=FDCAN2_RX
PB6.GPIOParameters=GPIO_Label
PB6.GPIO_Label=OUT_5
PB6.Signal=S_TIM4_CH1
PB7.GPIOParameters=GPIO_Label
PB7.GPIO_Label=OUT_6
PB7.Signal=S_TIM4_CH2
PB8.GPIOParameters=GPIO_Label
PB8.GPIO_Label=OUT_7
PB8.Signal=S_TIM4_CH3
PB9.GPIOParameters=GPIO_Label
PB9.GPIO_Label=OUT_8
PB9.Signal=S_TIM4_CH4
PC13.GPIOParameters=GPIO_Label
PC13.GPIO_Label=BTN_USR
PC13.Signal=GPIO_Input
PC14-OSC32_IN\ (PC14).Mode=LSE-External-Oscillator
PC14-OSC32_IN\ (PC14).Signal=RCC_OSC32_IN
PC15-OSC32_OUT\ (PC15).Mode=LSE-External-Oscillator
PC15-OSC32_OUT\ (PC15).Signal=RCC_OSC32_OUT
PC6.GPIOParameters=GPIO_Label
PC6.GPIO_Label=STAT1_B
PC6.Signal=S_TIM2_CH3
PC7.GPIOParameters=GPIO_Label
PC7.GPIO_Label=OUT_2
PC7.Signal=S_TIM3_CH2
PD0.Mode=FDCAN_Activate
PD0.Signal=FDCAN1_RX
PD1.Mode=FDCAN_Activate
PD1.Signal=FDCAN1_TX
PF0-OSC_IN\ (PF0).Mode=HSE-External-Oscillator
PF0-OSC_IN\ (PF0).Signal=RCC_OSC_IN
PF1-OSC_OUT\ (PF1).Mode=HSE-External-Oscillator
PF1-OSC_OUT\ (PF1).Signal=RCC_OSC_OUT
RCC.HSE_VALUE=8000000
RCC.SYSCLKFreq_VALUE=16000000
board=custom

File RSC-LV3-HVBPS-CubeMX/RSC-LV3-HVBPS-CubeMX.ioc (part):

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Mcu.Name=STM32G0B1C(B-C-E)Tx
Mcu.Package=LQFP48
Mcu.UserName=STM32G0B1CBTx
PA0.GPIOParameters=GPIO_Label
PA0.GPIO_Label=V_SENSE_5
PA0.Mode=IN0
PA0.Signal=ADC1_IN0
PA1.GPIOParameters=GPIO_Label
PA1.GPIO_Label=V_SENSE_12
PA1.Mode=IN1
PA1.Signal=ADC1_IN1
PA10.GPIOParameters=GPIO_Label
PA10.GPIO_Label=STAT0_B
PA10.Signal=S_TIM1_CH3
PA11\ [PA9].Mode=Device
PA11\ [PA9].Signal=USB_DM
PA12\ [PA10].Mode=Device
PA12\ [PA10].Signal=USB_DP
PA13.Mode=Serial_Wire
PA13.Signal=SYS_SWDIO
PA14-BOOT0.Mode=Serial_Wire
PA14-BOOT0.Signal=SYS_SWCLK
PA15.GPIOParameters=GPIO_Label
PA15.GPIO_Label=STAT1_R
PA15.Signal=S_TIM2_CH1_ETR
PA2.GPIOParameters=GPIO_Label
PA2.GPIO_Label=E_STOP_SENSE
PA2.Signal=GPIO_Input
PA3.GPIOParameters=GPIO_Label
PA3.GPIO_Label=E_STOP_SWITCH_LED
PA3.Signal=GPIO_Output
PA4.GPIOParameters=GPIO_Label
PA4.GPIO_Label=MAIN_CONTACTOR_ENABLE
PA4.Signal=GPIO_Output
PA5.GPIOParameters=GPIO_Label
PA5.GPIO_Label=BMS_DE_SENSE
PA5.Signal=GPIO_Input
PA6.GPIOParameters=GPIO_Label
PA6.GPIO_Label=MODULE_LED
PA6.Signal=GPIO_Output
PA8.GPIOParameters=GPIO_Label
PA8.GPIO_Label=STAT0_R
PA8.Signal=S_TIM1_CH1
PA9.GPIOParameters=GPIO_Label
PA9.GPIO_Label=STAT0_G
PA9.Signal=S_TIM1_CH2
PB13.Mode=FDCAN_Activate
PB13.Signal=FDCAN2_TX
PB3.GPIOParameters=GPIO_Label
PB3.GPIO_Label=STAT1_G
PB3.Signal=S_TIM2_CH2
PB5.Mode=FDCAN_Activate
PB5.Signal=FDCAN2_RX
PB6.GPIOParameters=GPIO_Label
PB6.GPIO_Label=FAN_1_TACH
PB6.Signal=GPIO_Input
PB7.GPIOParameters=GPIO_Label
PB7.GPIO_Label=FAN_1_PWM
PB7.Signal=GPIO_Output
PB8.GPIOParameters=GPIO_Label
PB8.GPIO_Label=FAN_2_TACH
PB8.Signal=GPIO_Input
PB9.GPIOParameters=GPIO_Label
PB9.GPIO_Label=FAN_2_PWM
PB9.Signal=GPIO_Output
PC13.GPIOParameters=GPIO_Label
PC13.GPIO_Label=BTN_USR
PC13.Signal=GPIO_Input
PC14-OSC32_IN\ (PC14).Mode=LSE-External-Oscillator
PC14-OSC32_IN\ (PC14).Signal=RCC_OSC32_IN
PC15-OSC32_OUT\ (PC15).Mode=LSE-External-Oscillator
PC15-OSC32_OUT\ (PC15).Signal=RCC_OSC32_OUT
PC6.GPIOParameters=GPIO_Label
PC6.GPIO_Label=STAT1_B
PC6.Signal=S_TIM2_CH3
PD0.Mode=FDCAN_Activate
PD0.Signal=FDCAN1_RX
PD1.Mode=FDCAN_Activate
PD1.Signal=FDCAN1_TX
PF0-OSC_IN\ (PF0).Mode=HSE-External-Oscillator
PF0-OSC_IN\ (PF0).Signal=RCC_OSC_IN
PF1-OSC_OUT\ (PF1).Mode=HSE-External-Oscillator
PF1-OSC_OUT\ (PF1).Signal=RCC_OSC_OUT
RCC.HSE_VALUE=8000000
RCC.SYSCLKFreq_VALUE=16000000
board=custom

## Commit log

2026-05-25 updated pinout, begin layout
2026-05-26 more layout work
2026-05-30 more work on layout
2026-06-03 add second CAN and backup domain components
2026-06-03 dual H/V compatible Molex footprints, corrected STM32 pinout
2026-06-03 initial routing
2026-06-03 more non-autorouting adjustments
2026-06-04 initial complete route
2026-06-06 silkscreen work
2026-06-06 more silkscreen and routing cleanup
2026-06-14 add zener diodes to inputs
2026-06-16 silkscreen tweaks
2026-06-16 add electrolytic capacitors and minor layout and silkscreen adjustments
2026-06-20 minor layout and silkscreen changes
2026-06-20 copy from SwitchSense, update schematic, begin redoing layout
2026-06-21 initial layout
2026-06-21 more layout and some initial routing
2026-06-21 full layout routing and silkscreen
2026-06-22 r0 final
